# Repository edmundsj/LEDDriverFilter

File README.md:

# LED Driver LC Filter

Filtering can provide shot-noise-limited performance from noisy drive electronics when driving LEDs with fixed currents. This LC filter is designed to aggressively lowpass filter an input current to a thorlabs LED to achieve shot-noise-limited output currents.

## Features
- Dual LC filter
- 1Hz -3dB frequency
- Shot-noise-limited performance at 1A drive current above 6Hz
- 1.3A maximum DC current (inductor-limited)
- Optional 0805 sense resistors at input and output
- Input screw terminal for connectorization to male M8-4 connector
- Output M8-4 female connector for connectorization to thorlabs LEDs
- Kicad schematic/PCB files, fabrication gerbers

Fig 0. 3D kicad rendering of PCB

[Fabricated PCB]
Fig 1. Image of fabricated PCB

## Simulations
Simulations were done in LTSpice using manufacturer specified parasitic values for the series resistance of capacitors (10mOhm) and inductors (1.27Ohm). 10mOhm sense resistor values were used.

Fig 2. Filter response from 0.1Hz - 100kHz

Fig 3. Filter response from 0.1Hz - 6Hz (first 20dB of rolloff). Note the -3dB frequency is approximately 1Hz.

## Test Data
Initial tests indicate the Thorlabs LEDD1B has current noise >20dB in excess of the shot noise limit when driving LEDs at 1A.

[TO BE ADDED]
Fig 4. Measured transfer function of LCR filter from 0.1Hz - 10kHz

[TO BE ADDED]
Fig 5. Measured noise spectra without filter

[TO BE ADDED]
Fig 6. Measured noise spectra with filter in series

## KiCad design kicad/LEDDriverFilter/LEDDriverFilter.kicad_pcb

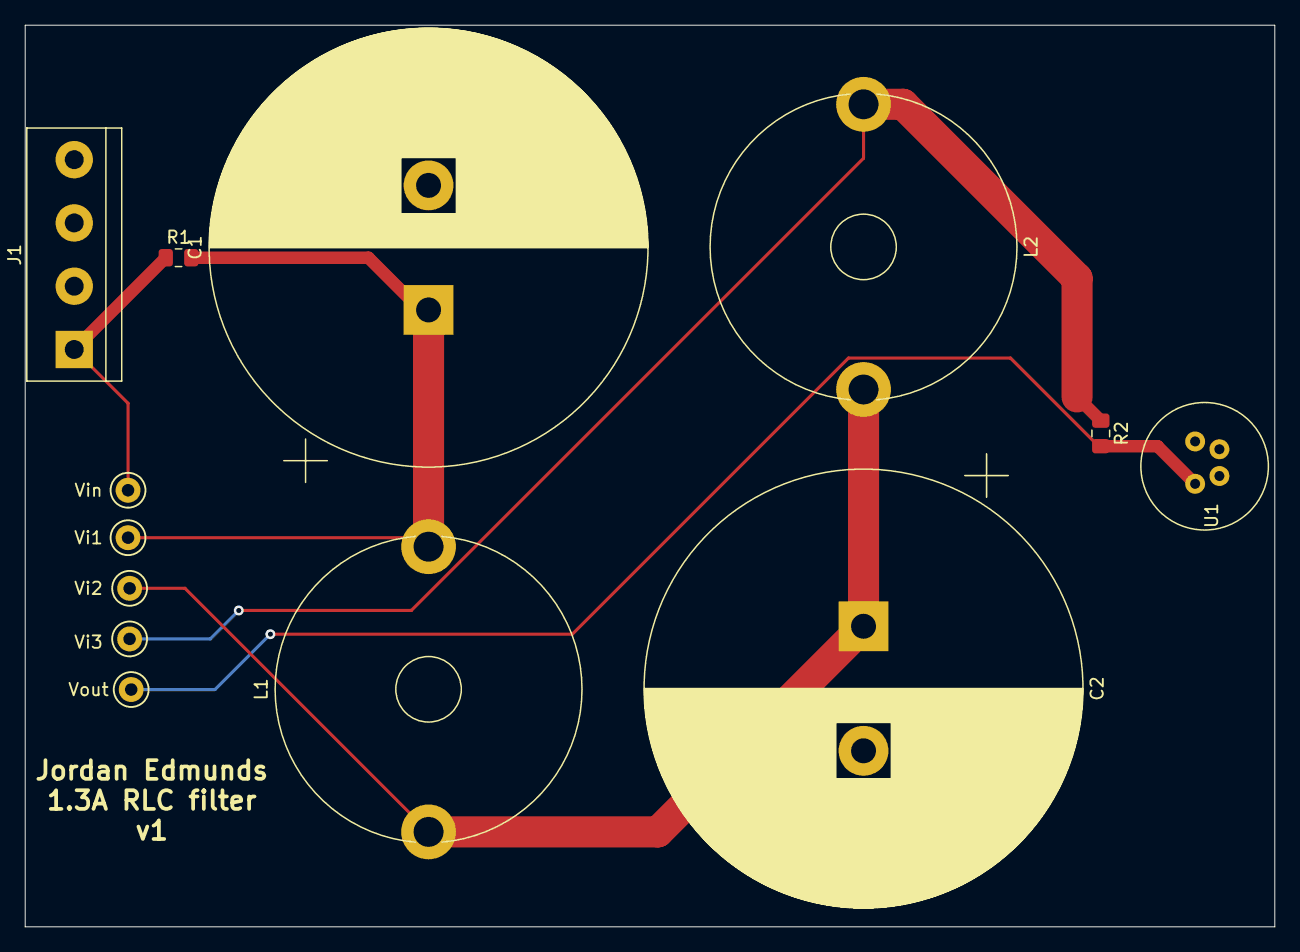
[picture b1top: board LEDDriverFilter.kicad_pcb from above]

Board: 2 copper layers, 100.3 x 72.4 mm, 13 parts (0 on the bottom side), 6 nets.

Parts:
C1, C2: 56m; CP_Radial_D35.0mm_P10.00mm_SnapIn
J1: Conn_01x04; TerminalBlock_bornier-4_P5.08mm
L1, L2: 3.3m; L_Radial_D24.4mm_P22.90mm_muRATA_1400series
R1: RSNSi; R_0805_2012Metric_Pad1.15x1.40mm_HandSolder
R2: RSNSo; R_0805_2012Metric_Pad1.15x1.40mm_HandSolder
TP1: Vin; TestPoint_Keystone_5000-5004_Miniature
TP2: Vi1; TestPoint_Keystone_5000-5004_Miniature
TP3: Vi2; TestPoint_Keystone_5000-5004_Miniature
TP4: Vi3; TestPoint_Keystone_5000-5004_Miniature
TP5: Vout; TestPoint_Keystone_5000-5004_Miniature
U1: m8-4; M8_4POS

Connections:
/Vi1: C1.1, L1.2, R1.2, TP2.1
/Vi2: C2.1, L1.1, L2.2, TP3.1
/Vi3: L2.1, R2.1, TP4.1
/Vin: J1.1, R1.1, TP1.1
/Vout: R2.2, TP5.1, U1.1
GND: C1.2, C2.2, J1.2, J1.3, J1.4, U1.2, U1.3, U1.4

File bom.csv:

Reference,Value,Kind,Quantity,Manufacturer #
"C1, C2",56m,Capacitor,2,SLPX563M016H4P3
J1,None,Screw Terminal,1,"TB007-508-04BE	"
"L1, L2",3.3m,Inductor,2,AIRD-03-332K
"R1, R2",10m,Resistor,1,None
TP1-5,None,Test Point,1,None
U1,None,M8 Female Connector,1,"T4043014041-000	"
None,None,M8 Male Cable,1,T4061120004-001

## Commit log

2021-05-07 added kicad board version 1, which will be fabricated. Added PCB rendering and LTSpice simulation files, along with simulation images
2022-02-16 added SPICE simulations, schematics, updated README
